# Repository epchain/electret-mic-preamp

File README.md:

# Electret microphone preamplifier

This is a Kicad EDA project of electret microphone preamplifier for improving
low-end electret microphone sound on a PC sound card.

Original schematic of preamplifier was found in this [article](https://www.ixbt.com/live/nikolay-suhov/komplementarnyy-si-ge-srpp-v-predusilitele-dlya-elektretnika-ili-master-klass-po-mikrokapu-11-v-praktike-audiofila_2.html)
and slightly modified. It uses general purpose PNP transistor instead of germanium
transistor. Also, PCB has footprint for small TRS connector.

This preamplifier has it's pros and cons:

**Pros:**

1. High gain
2. No need for external power supply. It uses only PC/laptop mic in.
3. Small number of accessible parts
4. Very small size, if built with SMD components

**Cons:**

1. Needs shielding. Without shielding there is too much noise.

# Implementation

My implementation uses BC847C/BC857C transistors and headset unidirectional
electret microphone, which requires without preamplifier +20 dB from sound
card and is unusable with this amplification due to high noise level.

Modified version of microphone looks like this:

Both preamplifier case and microphone boom are metallic and
internally connected to GND to act as a shield.

Preamplifier was successfully tested with a laptop sound card
with following electrical specs:

V = 1.8 V; I = 0.36 mA; R = 5 kOhm

# Modifications

Preamplifier schematic is simple and allows modifications. It's
possible to use other general purpose low-noise transistors,
suitable for audio amplification.
Following SOT23 transistors may be used:

  - BC846/BC856, BC847/BC857, BC848/BC858, BC849/BC859, BC850/BC860

BC849/BC859 and BC850/BC860 pairs should give best results.

KiCAD EDA project files are made to be fully autonomous.
If you want to keep files this way and modify them,
add your files in `device/lib` and link them to project
in a similar way to existing library elements.

# License

This project is licensed under [The Unlicense](LICENSE).
It contains library files from KiCAD EDA library in `device/lib`.
These files are licensed under [KiCAD EDA Libraries License](https://kicad-pcb.org/libraries/license/)

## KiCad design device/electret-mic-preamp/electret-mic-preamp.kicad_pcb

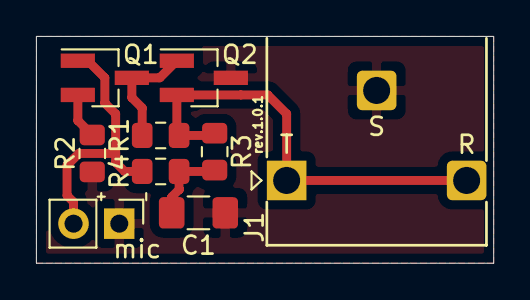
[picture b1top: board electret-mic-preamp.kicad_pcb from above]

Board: 2 copper layers, 25.4 x 12.6 mm, 9 parts (0 on the bottom side), 6 nets.

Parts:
C1: 100uF; C_1206_3216Metric_Pad1.42x1.75mm_HandSolder
J1: PJ-306M-2; Jack_3.5mm_PJ-306-2_Horizontal
Q1: BC847; SOT-23_Handsoldering
Q2: BC857; SOT-23_Handsoldering
R1: 33K; R_0805_2012Metric_Pad1.15x1.40mm_HandSolder
R2, R4: 1K; R_0805_2012Metric_Pad1.15x1.40mm_HandSolder
R3: 2K; R_0805_2012Metric_Pad1.15x1.40mm_HandSolder
mic: electret_mic; PinHeader_1x02_P2.54mm_Vertical

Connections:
GND: C1.2, J1.S, Q2.3, R2.1, mic.1
unnamed: C1.1, R3.2, R4.1
unnamed: J1.R, J1.T, Q2.2, R1.2, R3.1
unnamed: Q1.1, R4.2, mic.2
unnamed: Q1.2, R2.2
unnamed: Q1.3, Q2.1, R1.1

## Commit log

2020-10-01 Public release
